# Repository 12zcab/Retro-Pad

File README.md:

# Retro-Pad
What happens if a keyboard can emulate Retro Stuff?
Yah its just a simple keyboard but include a 4inch tft and speaker for Retro Emulation and Designed for myself.

## Tinkercad Link
https://www.tinkercad.com/things/bjJYySNUwrn-blekeyboard-esp32?sharecode=VCYoCMCinC_T4FhX9W5qrWKZ11Hd7W0aXTLVOQ6IZxw
## Zine Page Design
https://www.figma.com/design/CGgY6SRriEGCdJu8L95h5M/Retro-Pad-Zine-Page?node-id=0-1&t=7zGqFnisPlWxRSIn-1

## Images

## Notes
Erm the Emulator Part is not yet programmed as i haven't build it irl yet
I will work on it as I receive the grant to buy the ESP32
Also as i like Looking at PCBs so the case will be really simple

## Why I build this?
1.My Current Keyboard is DUMB
2.I think i like the touch of the 高特(erm in direct translation, High Special) Keystrokes
3.I also like to emulate 8086 or z80s with my pi and keyboard and a hdmi screen but i realized a single esp32 could have done all things in a single PCB

## What it can do?
1.Bluetooth/USB keyboard support
2.Configurable Macro Support
3.Key Layout Remap Support
4.Emulate Z80 CP/M :D
5.may be also as a mini Piano?(Erm yah cuz why not?)

## Component List
(For More Details,Please Refer to the BOM.csv.)
| Name | SpecName | Usage | Quantities |
|---|---|---|---|
| KeyStrokes | For My Self,高特青軸 (im not sure what its called in english)| For the Switches on Keyboard!| 77 |
| KeyCaps | Cherry Key Caps | Key Caps that you press on | Depends |
| ESP32 MCU board | ESP32 S3 N16R8 | A controller board that handles the TFT screen display and Bluetooth Communication | 1 |
| TFT Screen | TFT 4inch Screen Module with 14 Pins | A medium size TFT that display the Emulated Content and also Let me reconfigure the Keyboard with GUI | 1 |
| KeyStroke Hot Swappable Sockets | Kailh KeyStroke Sockets | for HotSwappable KeyStrokes!!! | 77 |
| Speaker | 2W3718 Speaker Module | Play Some Funny Sounds with esp32 | 1 |
| LED for Fn and Caps Signal | 5mm diameter THT leds | to show if u have Caps and Fn enabled or disabled. | 2 |
| LiBattery 3.7V | No Specific Name,just any Li Battery that can fit into the case | Any Capacity u want,3000mah suggested | 1 |
| LiBattery 3.7v-5v Protector Board and Charger Board | same as the name | Protecting ur Li-ion Battery from exploding | 1 |

Also prepare some 2.54 Dupont Socket and PinHeaders incase if u may disassemble it or replace some modules.

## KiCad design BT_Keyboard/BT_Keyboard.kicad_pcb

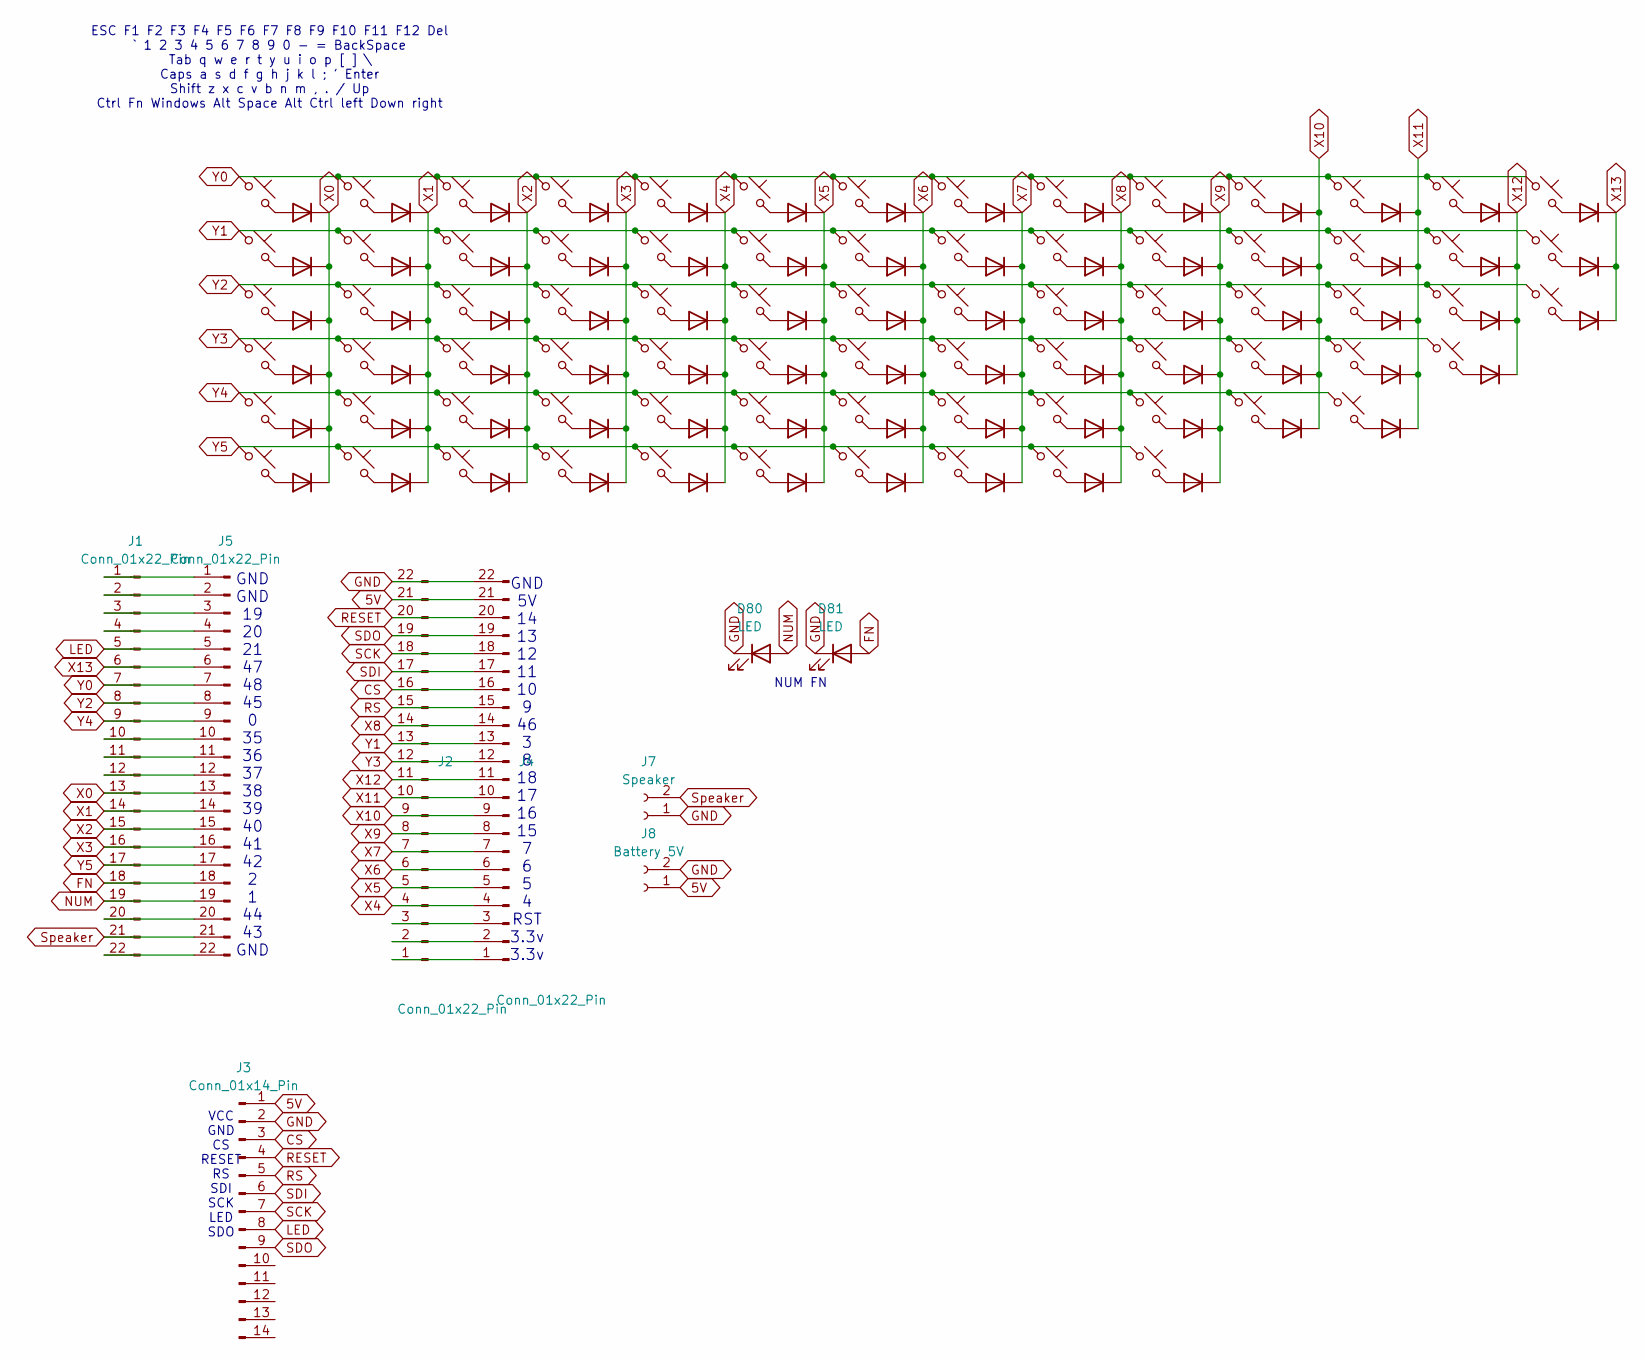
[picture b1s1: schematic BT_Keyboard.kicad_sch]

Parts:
D1, D2, D3, D4, D5, D6, D7, D8, D9, D10, D11, D12, D13, D14, D15, D16, D17, D18, D19, D20, D21, D22, D23, D24, D25, D26, D27, D28, D29, D30, D31, D32, D33, D34, D35, D36, D37, D38, D39, D40, D41, D42, D43, D44, D45, D46, D47, D48, D49, D50, D51, D52, D53, D54, D55, D56, D57, D58, D59, D60, D61, D62, D63, D64, D65, D66, D67, D68, D69, D70, D71, D72, D73, D74, D75, D76, D77: 1N4001; D_DO-41_SOD81_P10.16mm_Horizontal
D80, D81: LED; LED_D5.0mm
J1, J2, J4, J5: Conn_01x22_Pin; PinHeader_1x22_P2.54mm_Vertical
J3: Conn_01x14_Pin; PinHeader_1x14_P2.54mm_Vertical
J7: Speaker; PinSocket_1x02_P2.54mm_Vertical
J8: Battery 5V; PinSocket_1x02_P2.54mm_Vertical
SW1, SW2, SW3, SW4, SW5, SW6, SW7, SW8, SW9, SW10, SW11, SW12, SW13, SW14, SW15, SW16, SW17, SW18, SW19, SW20, SW21, SW22, SW23, SW24, SW25, SW26, SW27, SW30, SW31, SW32, SW33, SW34, SW35, SW36, SW37, SW38, SW39, SW40, SW41, SW42, SW44, SW45, SW46, SW47, SW48, SW49, SW50, SW51, SW52, SW53, SW54, SW57, SW58, SW59, SW60, SW61, SW62, SW63, SW64, SW65, SW66, SW67, SW68, SW69, SW70, SW71, SW72, SW73, SW74, SW75, SW76, SW77: SW_Push_45deg; SW_Hotswap_Kailh_MX_Plated_1.00u
SW28: Backspace; SW_Hotswap_Kailh_MX_Plated_1.75u
SW29: Tab; SW_Hotswap_Kailh_MX_Plated_1.25u
SW43: Cap; SW_Hotswap_Kailh_MX_Plated_1.50u
SW55: Enter; SW_Hotswap_Kailh_MX_Plated_2.00u
SW56: Shift; SW_Hotswap_Kailh_MX_Plated_2.00u

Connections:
5V: J2.21, J3.1, J4.21, J8.1
CS: J2.16, J3.3, J4.16
FN: D81.2 (A), J1.18, J5.18
GND: D80.1 (K), D81.1 (K), J2.22, J3.2, J4.22, J7.1, J8.2
LED: J1.5, J3.8, J5.5
NUM: D80.2 (A), J1.19, J5.19
unnamed: D1.2 (A), SW1.2
unnamed: D2.2 (A), SW2.2
unnamed: D3.2 (A), SW3.2
unnamed: D4.2 (A), SW4.2
unnamed: D5.2 (A), SW5.2
unnamed: D6.2 (A), SW6.2
unnamed: D7.2 (A), SW7.2
unnamed: D8.2 (A), SW8.2
unnamed: D9.2 (A), SW9.2
unnamed: D10.2 (A), SW10.2
unnamed: D11.2 (A), SW11.2
unnamed: D12.2 (A), SW12.2
unnamed: D13.2 (A), SW13.2
unnamed: D14.2 (A), SW14.2
unnamed: D15.2 (A), SW15.2
unnamed: D16.2 (A), SW16.2
unnamed: D17.2 (A), SW17.2
unnamed: D18.2 (A), SW18.2
unnamed: D19.2 (A), SW19.2
unnamed: D20.2 (A), SW20.2
unnamed: D21.2 (A), SW21.2
unnamed: D22.2 (A), SW22.2
unnamed: D23.2 (A), SW23.2
unnamed: D24.2 (A), SW24.2
unnamed: D25.2 (A), SW25.2
unnamed: D26.2 (A), SW26.2
unnamed: D27.2 (A), SW27.2
unnamed: D28.2 (A), SW28.2
unnamed: D29.2 (A), SW29.2
unnamed: D30.2 (A), SW30.2
unnamed: D31.2 (A), SW31.2
unnamed: D32.2 (A), SW32.2
unnamed: D33.2 (A), SW33.2
unnamed: D34.2 (A), SW34.2
unnamed: D35.2 (A), SW35.2
unnamed: D36.2 (A), SW36.2
unnamed: D37.2 (A), SW37.2
unnamed: D38.2 (A), SW38.2
unnamed: D39.2 (A), SW39.2
unnamed: D40.2 (A), SW40.2
unnamed: D41.2 (A), SW41.2
unnamed: D42.2 (A), SW42.2
unnamed: D43.2 (A), SW43.2
unnamed: D44.2 (A), SW44.2
unnamed: D45.2 (A), SW45.2
unnamed: D46.2 (A), SW46.2
unnamed: D47.2 (A), SW47.2
unnamed: D48.2 (A), SW48.2
unnamed: D49.2 (A), SW49.2
unnamed: D50.2 (A), SW50.2
unnamed: D51.2 (A), SW51.2
unnamed: D52.2 (A), SW52.2
unnamed: D53.2 (A), SW53.2
unnamed: D54.2 (A), SW54.2
unnamed: D55.2 (A), SW55.2
unnamed: D56.2 (A), SW56.2
unnamed: D57.2 (A), SW57.2
unnamed: D58.2 (A), SW58.2
unnamed: D59.2 (A), SW59.2
unnamed: D60.2 (A), SW60.2
unnamed: D61.2 (A), SW61.2
unnamed: D62.2 (A), SW62.2
unnamed: D63.2 (A), SW63.2
unnamed: D64.2 (A), SW64.2
unnamed: D65.2 (A), SW65.2
unnamed: D66.2 (A), SW66.2
unnamed: D67.2 (A), SW67.2
unnamed: D68.2 (A), SW68.2
unnamed: D69.2 (A), SW69.2
unnamed: D70.2 (A), SW70.2
unnamed: D71.2 (A), SW71.2
unnamed: D72.2 (A), SW72.2
unnamed: D73.2 (A), SW73.2
unnamed: D74.2 (A), SW74.2
unnamed: D75.2 (A), SW75.2
unnamed: D76.2 (A), SW76.2
unnamed: D77.2 (A), SW77.2
unnamed: J1.1, J5.1
unnamed: J1.2, J5.2
unnamed: J1.3, J5.3
unnamed: J1.4, J5.4
unnamed: J1.10, J5.10
unnamed: J1.11, J5.11
unnamed: J1.12, J5.12
unnamed: J1.20, J5.20
unnamed: J1.22, J5.22
unnamed: J2.1, J4.1
unnamed: J2.2, J4.2
unnamed: J2.3, J4.3
RESET: J2.20, J3.4, J4.20
RS: J2.15, J3.5, J4.15
SCK: J2.18, J3.7, J4.18
SDI: J2.17, J3.6, J4.17
SDO: J2.19, J3.9, J4.19
Speaker: J1.21, J5.21, J7.2
X0: D1.1 (K), D15.1 (K), D29.1 (K), D43.1 (K), D56.1 (K), D68.1 (K), J1.13, J5.13
X1: D2.1 (K), D16.1 (K), D30.1 (K), D44.1 (K), D57.1 (K), D69.1 (K), J1.14, J5.14
X2: D3.1 (K), D17.1 (K), D31.1 (K), D45.1 (K), D58.1 (K), D70.1 (K), J1.15, J5.15
X3: D4.1 (K), D18.1 (K), D32.1 (K), D46.1 (K), D59.1 (K), D71.1 (K), J1.16, J5.16
X4: D5.1 (K), D19.1 (K), D33.1 (K), D47.1 (K), D60.1 (K), D72.1 (K), J2.4, J4.4
X5: D6.1 (K), D20.1 (K), D34.1 (K), D48.1 (K), D61.1 (K), D73.1 (K), J2.5, J4.5
X6: D7.1 (K), D21.1 (K), D35.1 (K), D49.1 (K), D62.1 (K), D74.1 (K), J2.6, J4.6
X7: D8.1 (K), D22.1 (K), D36.1 (K), D50.1 (K), D63.1 (K), D75.1 (K), J2.7, J4.7
X8: D9.1 (K), D23.1 (K), D37.1 (K), D51.1 (K), D64.1 (K), D76.1 (K), J2.14, J4.14
X9: D10.1 (K), D24.1 (K), D38.1 (K), D52.1 (K), D65.1 (K), D77.1 (K), J2.8, J4.8
X10: D11.1 (K), D25.1 (K), D39.1 (K), D53.1 (K), D66.1 (K), J2.9, J4.9
X11: D12.1 (K), D26.1 (K), D40.1 (K), D54.1 (K), D67.1 (K), J2.10, J4.10
X12: D13.1 (K), D27.1 (K), D41.1 (K), D55.1 (K), J2.11, J4.11
X13: D14.1 (K), D28.1 (K), D42.1 (K), J1.6, J5.6
Y0: J1.7, J5.7, SW1.1, SW2.1, SW3.1, SW4.1, SW5.1, SW6.1, SW7.1, SW8.1, SW9.1, SW10.1, SW11.1, SW12.1, SW13.1, SW14.1
Y1: J2.13, J4.13, SW15.1, SW16.1, SW17.1, SW18.1, SW19.1, SW20.1, SW21.1, SW22.1, SW23.1, SW24.1, SW25.1, SW26.1, SW27.1, SW28.1
Y2: J1.8, J5.8, SW29.1, SW30.1, SW31.1, SW32.1, SW33.1, SW34.1, SW35.1, SW36.1, SW37.1, SW38.1, SW39.1, SW40.1, SW41.1, SW42.1
Y3: J2.12, J4.12, SW43.1, SW44.1, SW45.1, SW46.1, SW47.1, SW48.1, SW49.1, SW50.1, SW51.1, SW52.1, SW53.1, SW54.1, SW55.1
Y4: J1.9, J5.9, SW56.1, SW57.1, SW58.1, SW59.1, SW60.1, SW61.1, SW62.1, SW63.1, SW64.1, SW65.1, SW66.1, SW67.1
Y5: J1.17, J5.17, SW68.1, SW69.1, SW70.1, SW71.1, SW72.1, SW73.1, SW74.1, SW75.1, SW76.1, SW77.1

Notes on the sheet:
NUM FN
GND GND 19 20 21 47 48 45 0 35 36 37 38 39 40 41 42 2 1 44 43 GND
ESC F1 F2 F3 F4 F5 F6 F7 F8 F9 F10 F11 F12 Del ` 1 2 3 4 5 6 7 8 9 0 - = BackSpace Tab q w e r t y u i o p [ ] \ Caps a s d f g h j k l ; ' Enter Shift z x c v b n m , . / Up Ctrl Fn Windows Alt Space Alt Ctrl left Down right
VCC GND CS RESET RS SDI SCK LED SDO
GND 5V 14 13 12 11 10 9 46 3 8 18 17 16 15 7 6 5 4 RST 3.3v 3.3v

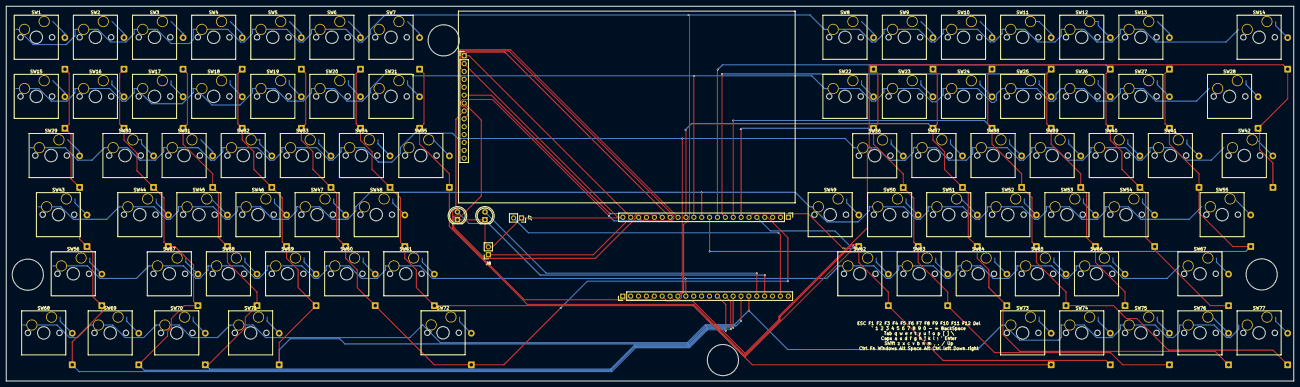
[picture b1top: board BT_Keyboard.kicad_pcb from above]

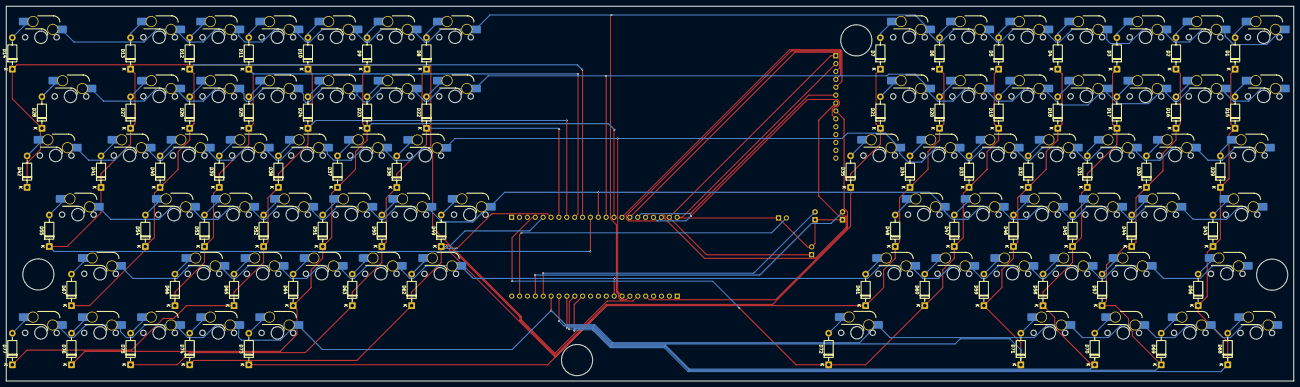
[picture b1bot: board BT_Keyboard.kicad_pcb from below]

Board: 2 copper layers, 414.8 x 120.7 mm, 161 parts (77 on the bottom side), 109 nets.

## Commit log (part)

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2026-05-23 Add submodule CherryKeyCap Modles
2026-06-10 Revise README.md for clarity and updates
2026-06-10 Add 3D printing and keycap list to KeycapsList.md
